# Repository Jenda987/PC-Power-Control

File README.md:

# PC-Power-Control

Remote startup, shutdown, reset and LED status monitoring for your PC with Home Assistant/ESPHome, powered by ESP32-C3 SuperMini board.

Control the power state of your PC and monitor LED status through Home Assistant by connecting your power, reset, and power LED front panel connectors to the appropriate pin pairs on ESP32-C3. Easily turn on and off your PC remotely using Home Assistant, keep track of the LED status. It's powered by +5V directly from the ATX connector.

## Use Cases

- Turn on, off and reset your PC remotely using Home Assistant.
- Set up automation based on time, motion, or any trigger to power on your PC.
- Utilize +5V from the ATX connector for powering the ESP32-C3 SuperMini, eliminating the need for an external power source.
- Achieve reliable control over your PC's power state without relying on wake-on-LAN.
- Enhance security by avoiding addons with admin access to your Windows PC. Use Home Assistant with ESPHome for seamless integration.
- Add voice commands via Home Assistant to control your PC using Google Assistant.

# Project Documentation

todo

## Getting Started

Follow the steps below to set up PC-Power-Control with your ESP32-C3 SuperMini:

1. **Hardware Connections:** Connect your power, reset, and power LED front panel connectors to the specified pin pairs on ESP32-C3 SuperMini. Also, connect the ESP32-C3 SuperMini to the +5V from the ATX connector.
   
2. **Power Up:** Provide power to the ESP32-C3 SuperMini directly from the ATX connector.
3. **Integration with Home Assistant using ESPHome:**
    - Install ESPHome on your ESP32-C3 SuperMini.
    - Configure ESPHome YAML file with the necessary settings, including pin assignments and Home Assistant integration.
    - Flash the ESPHome firmware to your ESP32-C3 SuperMini.

**ESPHome Template:** ``
todo
``

## PCB Specification
- Dimension: 23.75mm x 48.45mm
- PCB Thickness: 1.6mm

## Bill of Material

| Pos | References | Description | Value | Size | Quantity | Order Links \* | Notes |
|-----|------------|-------------|-------|------|----------|-------------|-------|
| 01 | ESP32-C3 SuperMini | ESP32-C3 SuperMini |  | ESP32-C3 | 1 | [Aliexpress](https://www.aliexpress.com/item/1005006127487371.html) | |
| 02 | U1, U2, U3 | PC817C SOP |  | PC817C SOP | 3 | [Aliexpress](https://www.aliexpress.com/item/1005003176703694.html) | |
| 03 | R1, R2 | Resistor | 330R | 0805 | 2 | [Aliexpress](https://www.aliexpress.com/item/1005001794062302.html)  | 
| 04 | R3 | Resistor | 2K2 | 0805 | 1 | [Aliexpress](https://www.aliexpress.com/item/1005001794062302.html)  | 
| 05 | J1 | Connector | P2 | JST XH2.54 | 1 | [Aliexpress](https://www.aliexpress.com/item/32954418743.html)  | 
| 06 | J2 | Connector | 2x6 | 2.54mm | 1 | [Aliexpress](https://www.aliexpress.com/item/1005003296463136.html)  | 

\* *I have not tested all parts using this order links, no guarantee that every linked component works. Aliexpress links are affiliate links, so i will get a small commission when you order using this link. This will help me with further projects. Thanks.*

## LICENSE

All content in this repository is is licensed under a [Creative Commons Attribution-NonCommercial-ShareAlike 4.0 International license](https://creativecommons.org/licenses/by-nc-sa/4.0/).

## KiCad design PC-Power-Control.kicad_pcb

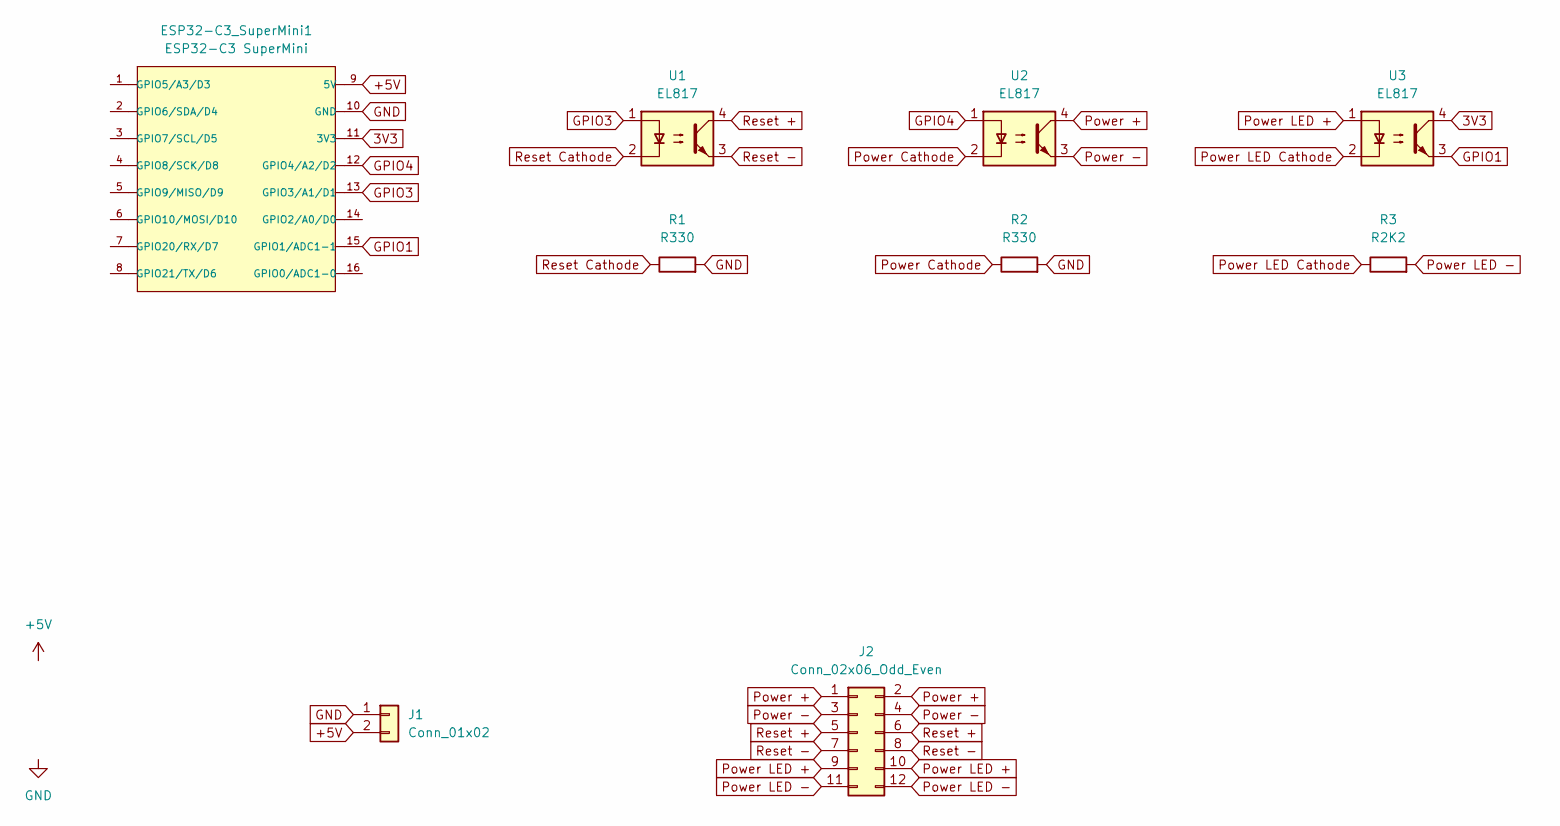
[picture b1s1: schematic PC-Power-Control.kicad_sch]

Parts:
ESP32-C3_SuperMini1: ESP32-C3 SuperMini; ESP3C3_supermini_COMBI
J1: Conn_01x02; JST_XH_B2B-XH-A_1x02_P2.50mm_Vertical
J2: Conn_02x06_Odd_Even; PinHeader_2x06_P2.54mm_Vertical
R1, R2: R330; R_0805_2012Metric_Pad1.20x1.40mm_HandSolder
R3: R2K2; R_0805_2012Metric_Pad1.20x1.40mm_HandSolder
U1, U2, U3: EL817; SOT254P975X400-4N

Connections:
3V3: ESP32-C3_SuperMini1.11 (3V3), U3.4
+5V: ESP32-C3_SuperMini1.9 (5V), J1.2
GND: ESP32-C3_SuperMini1.10 (GND), J1.1, R1.2, R2.2
GPIO1: ESP32-C3_SuperMini1.15 (GPIO1/ADC1-1), U3.3
GPIO3: ESP32-C3_SuperMini1.13 (GPIO3/A1/D1), U1.1
GPIO4: ESP32-C3_SuperMini1.12 (GPIO4/A2/D2), U2.1
Power +: J2.1, J2.2, U2.4
Power -: J2.3, J2.4, U2.3
Power Cathode: R2.1, U2.2
Power LED +: J2.9, J2.10, U3.1
Power LED -: J2.11, J2.12, R3.2
Power LED Cathode: R3.1, U3.2
Reset +: J2.5, J2.6, U1.4
Reset -: J2.7, J2.8, U1.3
Reset Cathode: R1.1, U1.2

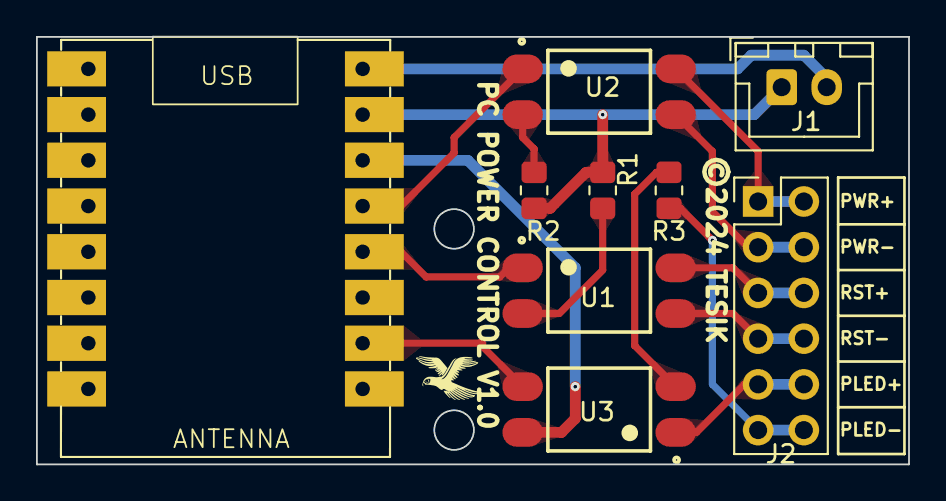
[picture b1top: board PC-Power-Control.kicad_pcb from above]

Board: 2 copper layers, 48.5 x 23.7 mm, 9 parts (0 on the bottom side), 15 nets.

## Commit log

2024-02-01 initial

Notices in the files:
PC-Power-Control.kicad_pcb:
©2024 TESIK
